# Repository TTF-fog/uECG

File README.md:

# uECG
a tiny board (18.92 × 18.60 mm) for wireless ECG signal capture and transmission.

HJ-840 (nRF52840) + AD8232 + LSM6DSRTR / STR-C

[View Board](https://pcbview.io/?github=https%3A%2F%2Fgithub.com%2FTTF-fog%2FuECG%2Fblob%2FHEAD%2FuECG.PcbDoc) or use [Altium Viewer](https://www.altium.com/viewer/) for a complete overview.

files:
- [Schematic](Sheet1.SchDoc)
- [PCB](uECG.PcbDoc)
## Why I made it
school project, need i say more? i did, however, find working in such a space constraint very enjoyable -- defo a board i'm proud of. 

## PCB design
4L, S + G + G + S, meant for JLC's 3313 stackup

> top layer

> bottom layer 

## Schematic

## Renders

> top side

> bottom side

## Wiring diagram

## Bill of materials
# Unified uECG BOM

| Category | Designators | Description | MPN | JLCPCB part | Link | Qty per PCB | Order qty | Total USD | Notes |
| :----------- | :------------------ | :--------------------------- | :----------------------- | :-------------- | :--- | :-------------- | :------------ | :------------ | :------------------------------- |
| Component | C1,C4 | 1uF25VX5R0402 | CL05A105KA5NQNC | C52923 | https://www.lcsc.com/search?q=C52923 | 2 | 20 | 0.0920 |  |
| Component | C5,C6 | 2.2uF16VX5R0402 | CL05A225KO5NQNC | C170151 | https://www.lcsc.com/search?q=C170151 | 2 | 20 | 0.3980 |  |
| Component | C7 | 10uF25VX5R0603 | CL10A106MA8NRNC | C96446 | https://www.lcsc.com/search?q=C96446 | 1 | 20 | 0.6520 |  |
| Component | C10,C11,C9 | 4.7uF16VX5R0402 | CL05A475MO5NUNC | C318563 | https://www.lcsc.com/search?q=C318563 | 3 | 40 | 0.7760 |  |
| Component | C13,C15,C2,C3 | 100nF16VX7R0402 | CL05B104KO5NNNC | C1525 | https://www.lcsc.com/search?q=C1525 | 4 | 40 | 0.1160 |  |
| Component | C14 | 1nF100VC0G0402 | 0402B102K500NT | C1523 | https://www.lcsc.com/search?q=C1523 | 1 | 20 | 0.0340 |  |
| Component | C16 | 6.8nF50VX7R0402 | CC0402KRX7R9BB682 | C93654 | https://www.lcsc.com/search?q=C93654 | 1 | 20 | 0.0240 |  |
| Component | C17 | 2.7nF50VX7R0402 | 0402B272K500NT | C45185 | https://www.lcsc.com/search?q=C45185 | 1 | 20 | 0.0920 |  |
| Component | D1,D2 | ESD321DPYR | ESD321DPYR | C2868952 | https://www.lcsc.com/search?q=C2868952 | 2 | 8 | 0.8864 |  |
| Component | DS1 | WhiteLED | 16-213SDRC/S530-A3/TR8 | C71911 | https://www.lcsc.com/search?q=C71911 | 1 | 10 | 0.3280 |  |
| Component | J1 | 2-pinright-angleheader | 705530106 | C588446 | https://www.lcsc.com/search?q=C588446 | 1 | 0 | 0.0000 | Not ordered; cost excluded |
| Component | J3 | 3-pinright-angleheader | 705530002 | C505296 | https://www.lcsc.com/search?q=C505296 | 1 | 0 | 0.0000 | Not ordered; cost excluded |
| Component | R1 | 1k0.1%62.5mW | 0402WGF1001TCE | C11702 | https://www.lcsc.com/search?q=C11702 | 1 | 20 | 0.0220 |  |
| Component | R2,R4,R10,R11,R3 | 10k0.1%100mW / 10k1%62.5mW | 0402WGF1002TCE | C25744 | https://www.lcsc.com/search?q=C25744 | 5 | 25 | 0.0225 | Shared order line counted once |
| Component | R5 | 3k1%62.5mW | 0402WGF3001TCE | C25784 | https://www.lcsc.com/search?q=C25784 | 1 | 20 | 0.0260 |  |
| Component | R6 | 18k1%62.5mW | 0402WGF1802TCE | C25762 | https://www.lcsc.com/search?q=C25762 | 1 | 20 | 0.0260 |  |
| Component | R8,R9,R16,R17,R25 | 10M1%62.5mW | 0402WGF1005TCE | C26082 | https://www.lcsc.com/search?q=C26082 | 5 | 20 | 0.0240 |  |
| Component | R12,R13 | 5.1k1%62.5mW | 0402WGF5101TCE | C25905 | https://www.lcsc.com/search?q=C25905 | 2 | 20 | 0.0280 |  |
| Component | R14,R24 | 100k0.1%100mW | 0402WGF1003TCE | C25741 | https://www.lcsc.com/search?q=C25741 | 2 | 20 | 0.0180 |  |
| Component | R19,R20 | 330k1%62.5mW | 0402WGF3303TCE | C25778 | https://www.lcsc.com/search?q=C25778 | 2 | 20 | 0.0260 |  |
| Component | R21 | 360k1%62.5mW | 0402WGF3603TCE | C45956 | https://www.lcsc.com/search?q=C45956 | 1 | 20 | 0.0380 |  |
| Component | R22,R23,R27 | 1M1%62.5mW | 0402WGF1004TCE | C26083 | https://www.lcsc.com/search?q=C26083 | 3 | 21 | 0.0210 |  |
| Component | R26 | 332k1%333mW | 0603WAF3323T5E | C23139 | https://www.lcsc.com/search?q=C23139 | 1 | 20 | 0.0340 |  |
| Component | U1 | BQ25185DLHR | BQ25185DLHR | C19725033 | https://www.lcsc.com/search?q=C19725033 | 1 | 2 | 3.2864 |  |
| Component | U2 | MIC5528-3.3YMT-TR | MIC5528-3.3YMT-TR | C622490 | https://www.lcsc.com/search?q=C622490 | 1 | 2 | 1.0638 |  |
| Component | U3 | LSM6DSRTR | LSM6DSRTR | C784817 | https://www.lcsc.com/search?q=C784817 | 1 | 2 | 6.1438 |  |
| Component | U4 | HJ-840 | HJ-840 | C50052094 | https://www.lcsc.com/search?q=C50052094 | 1 | 2 | 15.9238 |  |
| Component | U5 | AD8232ACPZ-R7 | AD8232ACPZ-R7 | C43216 | https://www.lcsc.com/search?q=C43216 | 1 | 2 | 13.4298 |  |
| Component | U7 | TYPE-C-31-M-12 | TYPE-C-31-M-12 | C165948 | https://www.lcsc.com/search?q=C165948 | 1 | 2 | 0.3738 |  |
| Fee |  | PCB fabrication |  |  |  |  |  | 8.0000 |  |
| Fee |  | Setup fee |  |  |  |  |  | 51.5000 |  |
| Fee |  | Stencil |  |  |  |  |  | 16.5400 |  |
| Fee |  | Feeders loading fee |  |  |  |  |  | 41.8500 |  |
| Fee |  | SMT assembly |  |  |  |  |  | 1.9600 |  |
| Fee |  | X-ray inspection |  |  |  |  |  | 6.6000 |  |
| Fee |  | Packaging fee |  |  |  |  |  | 0.5000 |  |
| Fee |  | UPS Express Saver shipping |  |  |  |  |  | 9.0000 |  |
| Total |  |  |  |  |  |  |  | 179.8553 |  |

### TODO
- manufacturability
- retune USB impedance

Made in Altium Designer 26.

### AI Declaration
used for dummy work -- compiling the BOM, some research, directory organisation and reformatting one symbol.
All design assets are otherwise created by me

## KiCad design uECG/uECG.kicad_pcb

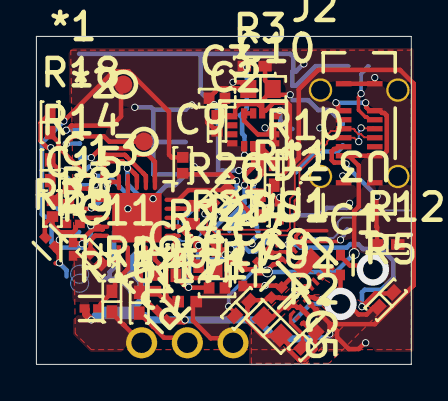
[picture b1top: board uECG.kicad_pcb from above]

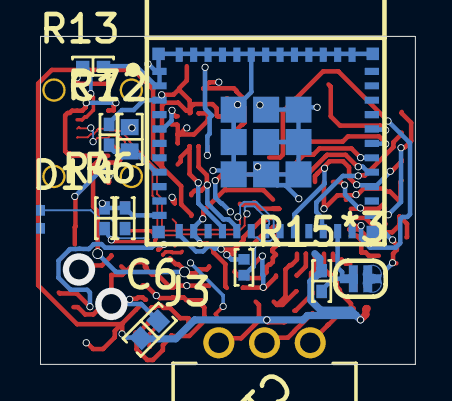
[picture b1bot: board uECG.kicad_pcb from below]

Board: 4 copper layers, 20.8 x 18.2 mm, 56 parts (12 on the bottom side), 43 nets.

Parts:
*1, *2: TestPoint_Small; TestPoint_Pad_D1.0mm
*3: SolderJumper_2_Open; SolderJumper-2_P1.3mm_Open_RoundedPad1.0x1.5mm
C1, C7: 0402YD105MAT2A; FP-0402-L_1_0_1-W_0_5_0_1-MFG
C2, C3, C13, C15: 0.1 µF; CAP 0402_1005
C5, C6: 2.2 µF; CAP 0603_1608
C8: C0402C106M9PACTU; FP-C0402C106M9PACTU-MFG
C9, C11: 4.7 µF; CAP 0402_1005
C10: 22 µF; CAP 0603_1608
C12: 1 µF; CAP 0603_1608
C14: 1000 pF; CAP 0402_1005
C16: 6800 pF; CAP 0402_1005
C17: 2700 pF; CAP 0402_1005
D1, D2: ESD321DPYR; FP-DPY0002A-MFG
DS1: 16-219A/T2D-AR2T1QY/3T; EVRL-0402-2_V
J2: MUP-U23010-02; MUPU2301002
J3: 0705530002; MOLEX SDA-70553-3PIN
R1: 1 kOhms; RES 0402_1005
R2, R4, R7, R10, R11, R15, R18: 10 kOhms; RES 0402_1005
R3: 10K; RES 0402_1005
R5: 3 kOhms; RES 0402_1005
R6: 18 kOhms; RES 0402_1005
R8, R9, R25: CRGCQ0402J10M; FP-CRGCQ0402-IPC_C
R12, R13: 5.1K; RES 0402_1005
R14, R24: 100 kOhms; RES 0402_1005
R16, R17: 10M; FP-CRGCQ0402-IPC_C
R19, R20: 330 kOhms; RES 0402_1005
R21: CRCW0402360KJNED; RESC1005X40X25ML05T05
R22, R23, R27: 1 MOhms; RES 0402_1005
R26: 332 kOhms; RESC1005X40X25ML05T05
U1: BQ25185DLHR; WSON-10_L2.2-W2.0-P0.40-BL-EP_TI_DLH0010A
U2: MIC5528-3.3YMT-TR; FP-TDFN1212-6LD-PL-1-MFG
U3: LSM6DSRTR; FP-LGA-14L-DM00249496-MFG
U4: ESP32-C6-MINI-1-N4; WIFIM-SMD_61P-L16.6-W13.2-P0.80-ESP32-C6-MINI-1-N4
U5: AD8232ACPZ-WP; FP-CP-20-8-IPC_A

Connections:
3V3: C2.2, C3.2, C6.2, C10.2, C13.2, R3.1, R7.1, R8.1, R10.2, R11.2, R15.2, R16.1, R17.1, R18.2, U2.1, U2.2, U3.5, U3.8, U4.3, U5.15, U5.17
CC1: J2.A5, R12.2
CC2: J2.B5, R13.2
D_N: D2.1, J2.A7, J2.B7, U4.17
D_P: D1.1, J2.A6, J2.B6, U4.18
GND: *3.1, C1.2, C2.1, C3.1, C5.1, C6.1, C7.2, C8.2, C10.1, C12.1, C13.1, C15.1, D1.2, D2.2, J2.A1, J2.A12, J2.B1, J2.B12, R4.1, R5.1, R6.1, R12.1, R13.1, R14.1, R25.1, U1.4, U1.5, U1.11, U2.3, U2.7, U3.1, U3.2, U3.3, U3.6, U3.7, U4.1, U4.2, U4.11, U4.14, U4.36, U4.37, U4.38, U4.39, U4.40, U4.41, U4.42, U4.43, U4.44, U4.45, U4.46, U4.47, U4.48, U4.49, U4.50, U4.51, U4.52, U4.53, U5.14, U5.16, U5.21
HPDRIVE: C11.1, U5.1
HPSENSE: C11.2, R9.2, U5.20
IAOUT: C9.1, R9.1, U5.19
INT1: U3.4, U4.5
IO1: U4.29, U5.11
IO2: U4.28, U5.12
IO3: R14.2, U4.20, U4.27, U5.13
Net*1_1: *1.1, U4.31
Net*2_1: *2.1, U4.30
Net*3_2: *3.2, R15.1, U4.23
NetC12_2: C12.2, R7.2, U4.8
NetC14_1: C14.1, R21.1, U5.5
NetC14_2: C14.2, U5.4
NetC17_2: C17.2, R22.1, R23.1
NetDS1_1: DS1.1, R1.2
NetJ3_1: J3.1, R19.1
NetJ3_2: J3.2, R20.1
NetJ3_3: J3.3, R21.2
NetR2_1: R2.1, U2.4
NetR3_2: R3.2, U3.12
NetR4_2: R4.2, U1.6
NetR5_2: R5.2, U1.8
NetR6_2: R6.2, U1.\/
NetR16_2: R16.2, R19.2, U5.2
NetR17_2: R17.2, R20.2, U5.3
NetR18_1: R18.1, U4.22
OPAM+: C16.2, R23.2, U5.7
OPAM-: R26.1, R27.2, U5.9
REFIN: C15.2, R8.2, R25.2, U5.18
SCL: R11.1, U3.13, U4.16
SDA: R10.1, U3.14, U4.15
STATA1: DS1.2, U1.9
SW: C9.2, R22.2, R24.2, U5.6
VBUS: C7.1, J2.A4, J2.A9, J2.B4, J2.B9, U1.10
VOUT: C5.2, C8.1, R1.1, R2.2, U1.1, U2.6
a0: C16.1, R24.1, R26.2, U4.12, U5.8
a1: C17.1, R27.1, U4.13, U5.10
